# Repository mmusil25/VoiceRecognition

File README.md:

# Voice Recognition Lock Box

### Team Members

Mark Musil (mmusil@pdx.edu), Amanda Voegtlin (voegtlin@pdx.edu), Samantha Fink (scleary@pdx.edu), Rawan Abdo (rabdo@pdx.edu)

## Project Description

For the Portland State University pre-capstone class (ECE 411) the team designed a voice-activated lockbox that can be used to protect belongings. Using the open source [speech-to-text library uSpeech] (https://github.com/arjo129/uSpeech) an AtMega32U4 was programmed to activate a solenoid in response to the diction of a password ("shore"). The potential market for such a product is adolescents with small belongings such as jewelry or diaries that they wish to protect. 

Please see the presentation file "Presentation_Group3.pdf" for a thorough description including block diagrams, functional flowcharts and more.

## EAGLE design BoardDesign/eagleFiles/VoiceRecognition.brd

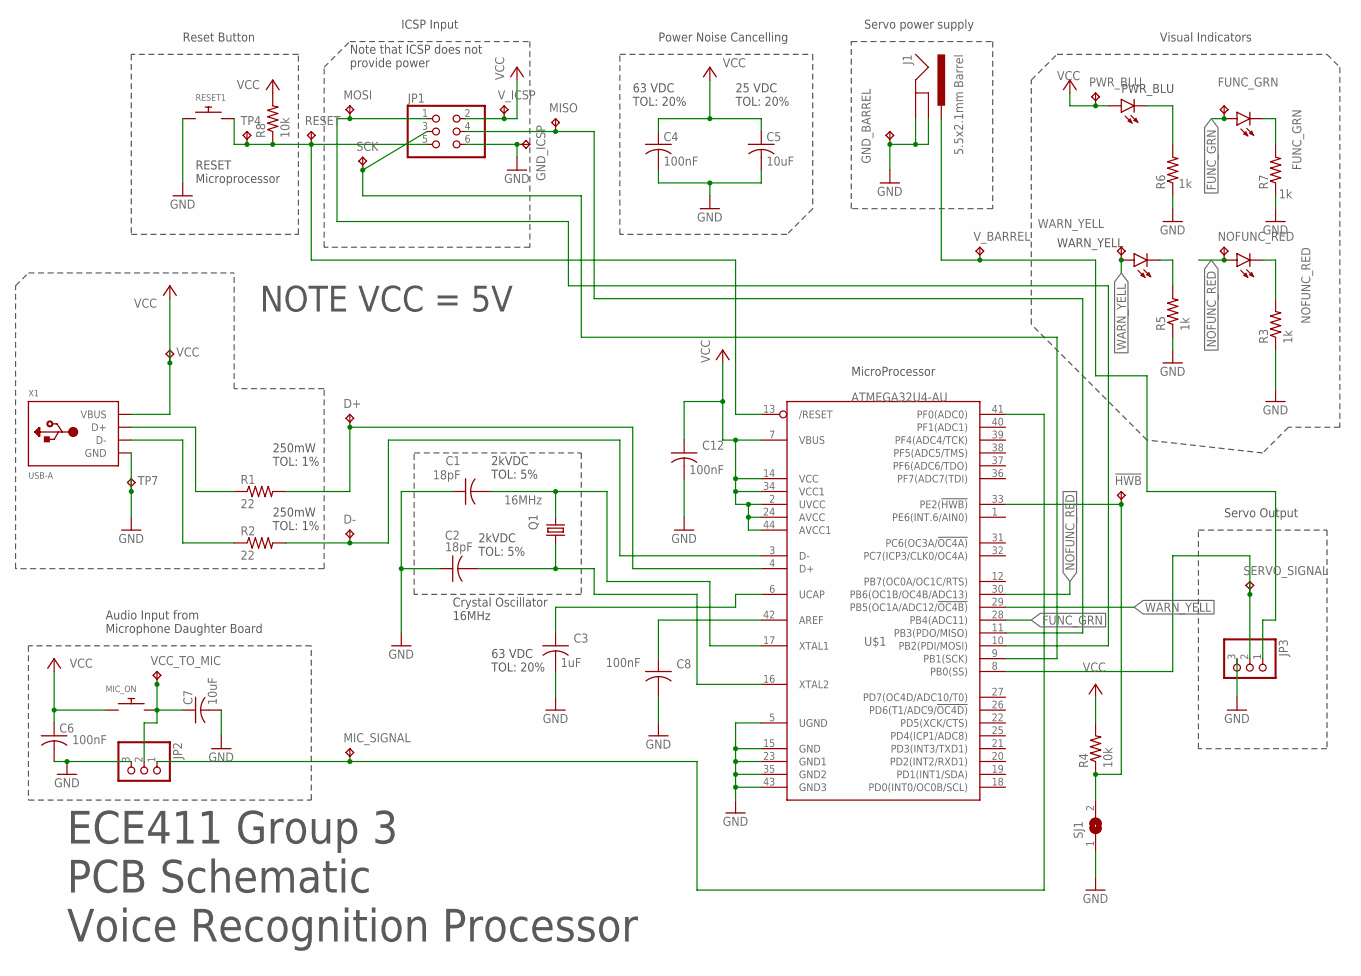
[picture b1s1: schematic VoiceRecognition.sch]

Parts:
!HWB: TPTP15SQ; TP15SQ
C1, C2: 18pF; C1206
C3: 1uF; C1206
C4, C6, C8, C12: 100nF; C1206
C5, C7: 10uF; C1206
D+: TPTP15SQ; TP15SQ
D-: TPTP15SQ; TP15SQ
FUNC_GRN: TPTP15SQ; TP15SQ
GND_BARREL: TPTP15SQ; TP15SQ
GND_ICSP: TPTP15SQ; TP15SQ
J1: 5.5x2.1mm Barrel; POWER_JACK_SMD
JP1: PINHD-2X3; 2X03
JP2, JP3: PINHD-1X3; 1X03
LED2, LED3, LED4: LEDSMT1206; 1206
MIC_ON: SWITCH_PUSHBUTTONC&K_KSS; BTN_CK_KSS
MIC_SIGNAL: TPTP15SQ; TP15SQ
MISO: TPTP15SQ; TP15SQ
MOSI: TPTP15SQ; TP15SQ
NOFUNC_RED: TPTP15SQ; TP15SQ
PWR-BLU: LEDSMT1206; 1206
PWR_BLU: TPTP15SQ; TP15SQ
Q1: 16MHz; CTS406
R1, R2: 22; M1206
R3, R5, R6, R7: 1k; M1206
R4, R8: 10k; M1206
RESET: TPTP15SQ; TP15SQ
RESET1: SWITCH_PUSHBUTTONC&K_KSS; BTN_CK_KSS
SCK: TPTP15SQ; TP15SQ
SERVO_SIGNAL: TPTP15SQ; TP15SQ
SJ1: SJW
TP4, TP7: TPTP15SQ; TP15SQ
U$1: ATMEGA32U4-AU; TQFP44
VCC: TPTP15SQ; TP15SQ
VCC_TO_MIC: TPTP15SQ; TP15SQ
V_BARREL: TPTP15SQ; TP15SQ
V_ICSP: TPTP15SQ; TP15SQ
WARN_YELL: TPTP15SQ; TP15SQ
X1: USB-A; MOLEX_480371000

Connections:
FUNC_GRN: FUNC_GRN.TP, LED2.A, U$1.28 (PB4(ADC11))
GND: C1.1, C2.1, C3.2, C4.2, C5.2, C6.2, C7.2, C8.2, C12.2, GND_BARREL.TP, GND_ICSP.TP, J1.GND (GNDBREAK), J1.P$4 (GND), JP1.6, JP2.3, JP3.3, R3.1, R5.1, R6.1, R7.1, RESET1.P$1, SJ1.1, TP7.TP, U$1.5 (UGND), U$1.15 (GND), U$1.23 (GND1), U$1.35 (GND2), U$1.43 (GND3), X1.4 (GND)
HWB: !HWB.TP, R4.1, SJ1.2, U$1.33 (PE2(!HWB))
MIC_SIGNAL: JP2.1, MIC_SIGNAL.TP, U$1.41 (PF0(ADC0))
unnamed: C3.1, U$1.6 (UCAP)
unnamed: JP1.3, SCK.TP, U$1.9 (PB1(SCK))
unnamed: R1.1, X1.3 (D+)
unnamed: PWR-BLU.C, R6.2
unnamed: LED2.C, R7.2
unnamed: LED4.C, R5.2
unnamed: LED3.C, R3.2
unnamed: R2.1, X1.2 (D-)
unnamed: D+.TP, R1.2, U$1.4 (D+)
unnamed: JP1.1, MOSI.TP, U$1.10 (PB2(PDI/MOSI))
unnamed: C8.1, U$1.42 (AREF)
unnamed: C7.1, JP2.2, MIC_ON.P$2, VCC_TO_MIC.TP
unnamed: C1.2, Q1.3 (2), U$1.17 (XTAL1)
unnamed: JP1.4, MISO.TP, U$1.11 (PB3(PDO/MISO))
unnamed: D-.TP, R2.2, U$1.3 (D-)
unnamed: C2.2, Q1.1, U$1.16 (XTAL2)
NOFUNC_RED: LED3.A, NOFUNC_RED.TP, U$1.30 (PB6(OC1B/OC4B/ADC13))
RST: JP1.5, R8.1, RESET.TP, RESET1.P$2, TP4.TP, U$1.13 (/RESET)
SERVO_POS: J1.VIN0 (PWR), JP3.1, V_BARREL.TP
SIGNAL: JP3.2, SERVO_SIGNAL.TP, U$1.8 (PB0(SS))
VCC: C4.1, C5.1, C6.1, C12.1, JP1.2, MIC_ON.P$1, PWR-BLU.A, PWR_BLU.TP, R4.2, R8.2, U$1.2 (UVCC), U$1.7 (VBUS), U$1.14 (VCC), U$1.24 (AVCC), U$1.34 (VCC1), U$1.44 (AVCC1), VCC.TP, V_ICSP.TP, X1.1 (VBUS)
WARN_YELL: LED4.A, U$1.29 (PB5(OC1A/ADC12/!OC4B)), WARN_YELL.TP

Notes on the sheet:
MicroProcessor
Power Noise Cancelling
ICSP Input
Visual Indicators
Audio Input from Microphone Daughter Board
ECE411 Group 3 PCB Schematic Voice Recognition Processor
Servo Output
63 VDC TOL: 20%
25 VDC TOL: 20%
2kVDC TOL: 5%
250mW TOL: 1%
Note that ICSP does not provide power
Crystal Oscillator 16MHz
RESET Microprocessor
Reset Button
PWR_BLU
WARN_YELL
Servo power supply
NOTE VCC = 5V

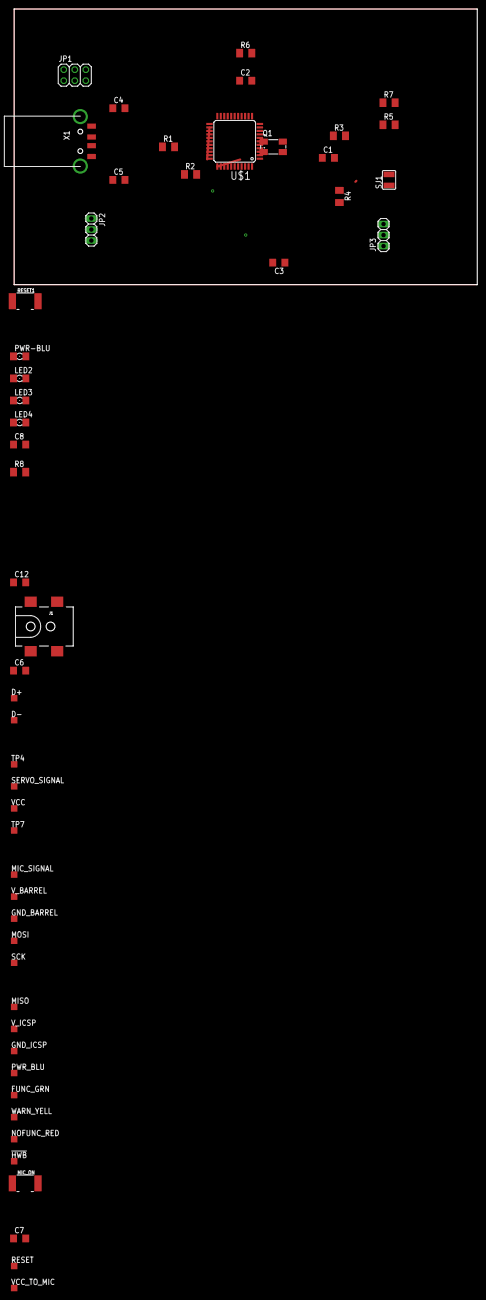
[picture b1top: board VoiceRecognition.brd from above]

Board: 2 copper layers, 106.7 x 63.5 mm, 52 parts (0 on the bottom side), 26 nets.

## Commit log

2018-10-05 The firs commit, it contains the bill of materials. Please leave commit notes, thank you
2018-10-05 Added about 9 components to the BOM
2018-10-10 Update BillOFMaterials.ods
    Added op-amp information. Also changed formatting so all monetary values had dollar signs because I'm a stickler.
2018-10-10 Update BillOFMaterials.ods
    Corrected price for LM386; numbers are difficult late at night.
2018-10-11 New BOM
2018-10-12 Update BillOFMaterials.ods
    * Changed "Prototype" tab to "Final Product" tab.
    * Added Prototype materials, including purchase date.
    * Updated "Admin" tab to include more purchase information, and to allow the spreadsheet to keep a running tally of individual purchase values.
2018-10-13 New bill of materials is up
2018-10-16 Adding in-progess EagleCAD schem
    EagleCAD schem in progress.
2018-10-22 small updates
    Updated file extension and schematic.
2018-10-24 Added Schematic Version 1
2018-10-26 Added latest schematic and board files
2018-10-28 Added some EagleCAD schematic updates
2018-11-01 Brought sanity back to our git
2018-11-01 Create Box Design
    This is my plan for the actual box design, will update as I go
2018-11-02 Add files via upload
    Arjo Chakavarty's phoneme table for calibration and debugging using the Debug sketch in USpeech 4.0
2018-11-02 Add files via upload
    Phoneme reference output table for debugging and calibrating uSpeech on a given Arduino Uno.
2018-11-03 Rename Box Design to Rawan's Log
2018-11-03 Update and rename Rawan's Log to Rawan & Amanda Progress Log
2018-11-03 PCB Schematic completed
2018-11-03 Organized the file structure of this repository
2018-11-03 Performed the schematic ERC
2018-11-03 Rename Rawan & Amanda Progress Log to log/Rawan & Amanda Progress Log
2018-11-04 Completed the version 1 BOM
2018-11-04 Some organization and file management
2018-11-07 Board Update and Misc
    * Uploaded PCB board layout for review.
    * Updated names of some components to make them easier to identify on the schematic (LEDs, test points, etc.).
2018-11-08 Update DesignReview.odt
    Updated Design Review to reflect feedback from 11/7 meeting with Lee.
2018-11-08 Renamed file
    Because we need our team name in the files. :\
2018-11-08 Added Updated Board and BOM, note this will not be the final revision
2018-11-08 Added a few changes to the board per andrew's suggestion
2018-11-08 Added a connection to ground in the USB jack
2018-11-09 yeah
    * rearranged bypass caps to VCC
    * Added tolerances to bottom right of schem
2018-11-09 VCC caps + cosmetics
    * Moved vcc bias caps onto board.
    * Moved component names/values around for legibility.
    * Rerouted some wires for cosmetic purposes.
2018-11-09 Add files via upload
    Algorithm for final uspeech servo control code
2018-11-10 Vias & Ground Plane
    *Verified that all vias tied to GND were stiched. Wondering if we need additional ground stitching vias around the board?
2018-11-10 Purchased the completed BOM and thus updated the transaction history on the BOM to reflect the dollars amounts contributed by each member
2018-11-12 Create servocontrol_rawan
2018-11-12 Rename servocontrol_rawan to servocontrol_rawan.ino
2018-11-13 Update servocontrol_rawan.ino
    fixed errors made button work
2018-11-13 Rearranges
    * Moved some components around per Tom's suggestons. Edits from 11/12; forgot to push to git.,
2018-11-14 Additional Board Updates
    *Moved C1 so signals N$2 and N$22 (from crystal oscillator) would connect directly to processor instead of through a via. Signal wire is now wider than previous versions of the layout.
    * Moved a few GND wires around.
    * Added two additional GND stitching vias.
2018-11-15 Rearranged a few silkscreen labels on the layout
2018-11-15 Moved items away from edge of board.
    Moved the following items:
    * SERVO_OUT, RESET button
    * TP GND
    * VCC at bottom of board between TP VCC and MIC_INPUT
2018-11-15 Version number on board
    Put version number on board per oshpark instructions. Was not sure exactly what version it was; per Github, the file has been changed 10 times, so went with that.
2018-11-15 I wanna die.
    Files with names designated for Oshpark upload.
2018-11-15 asdf
    asdasfsadfsfd
2018-11-15 Final final finalize finale of the final board layout
2018-11-15 ERC/DRC Checks Complete on new board
2018-11-15 Create finalcodePrototype
    This lets the servo open when you say shoar
2018-11-21 Create 11-20-2018 working final code
2018-11-24 Added group decision matrix and practicum comparison guide
2018-11-26 Added DXF files for cutting stencils
    tcream will be a stencil for the top of the board, while bcream should be for the back of the board (I don't think we need it).
2018-12-01 This is a test of our three LEDs on the PCB
2018-12-02 Add files via upload
    Where to ground ~HWB so that Arduino can upload to it via USB.
2018-12-02 Add files via upload
    Where to place rocker switch to conditionally switch off ~HWB
2018-12-04 Create LAST FINAL CODE
2018-12-05 Added schematic image for presentation
2018-12-06 Create LICENSE
2018-12-06 Organization and uploaded the presentation

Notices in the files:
parts and their libraries:
SparkFun-Connectors: Licensing: Creative Commons ShareAlike 4.0 International - https://creativecommons.org/licenses/by-sa/4.0
